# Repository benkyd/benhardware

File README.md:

# BenHardware

A collection of hardware projects, primarily in KiCad

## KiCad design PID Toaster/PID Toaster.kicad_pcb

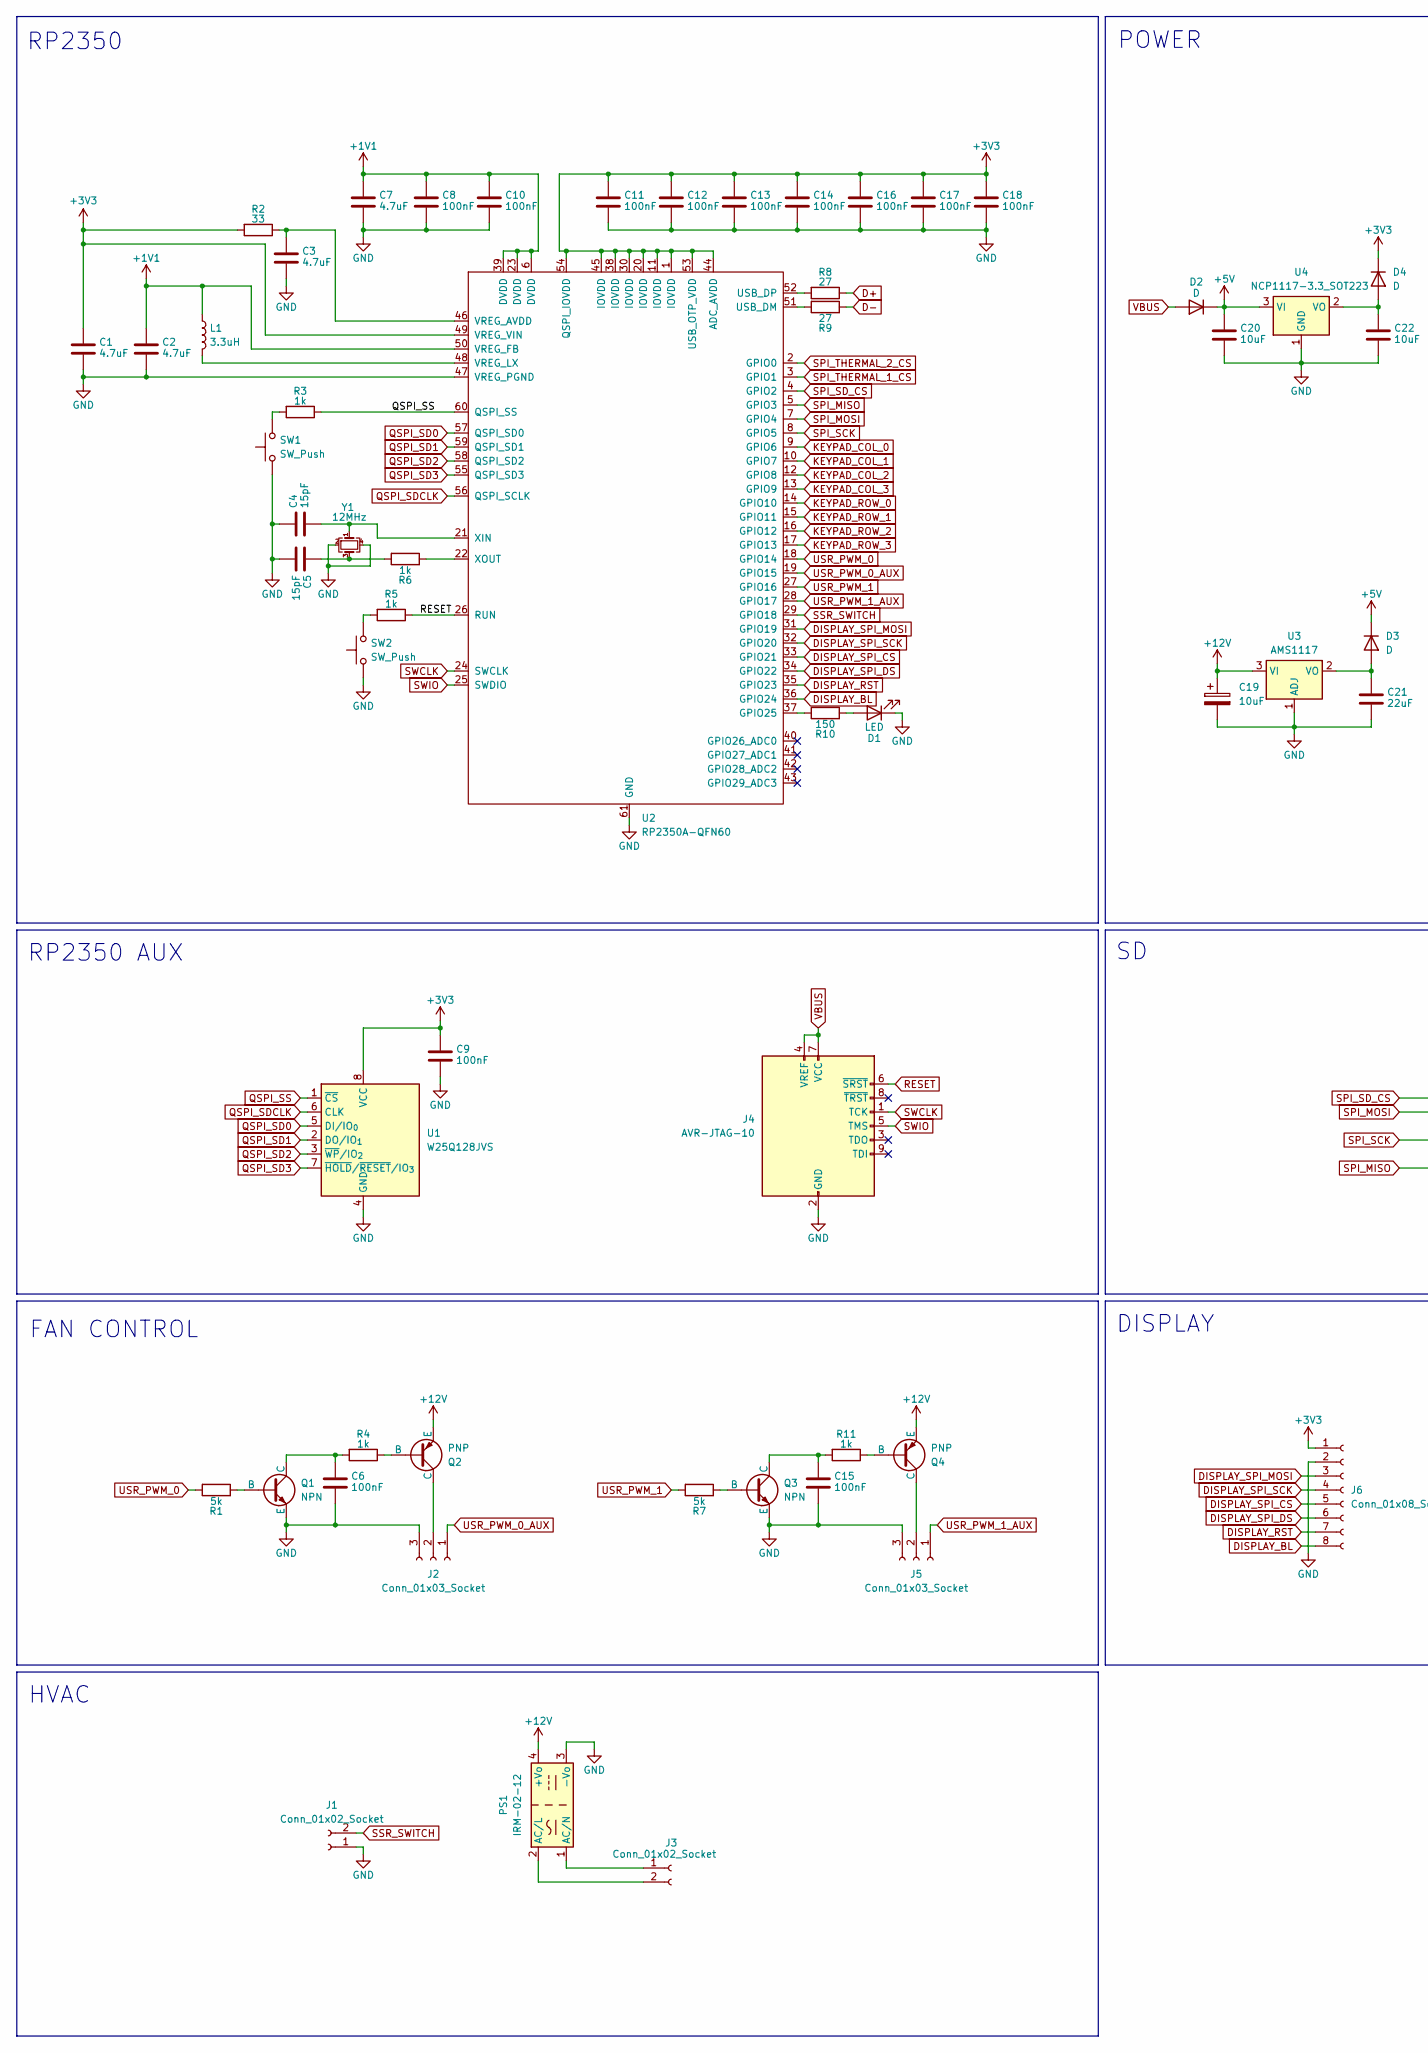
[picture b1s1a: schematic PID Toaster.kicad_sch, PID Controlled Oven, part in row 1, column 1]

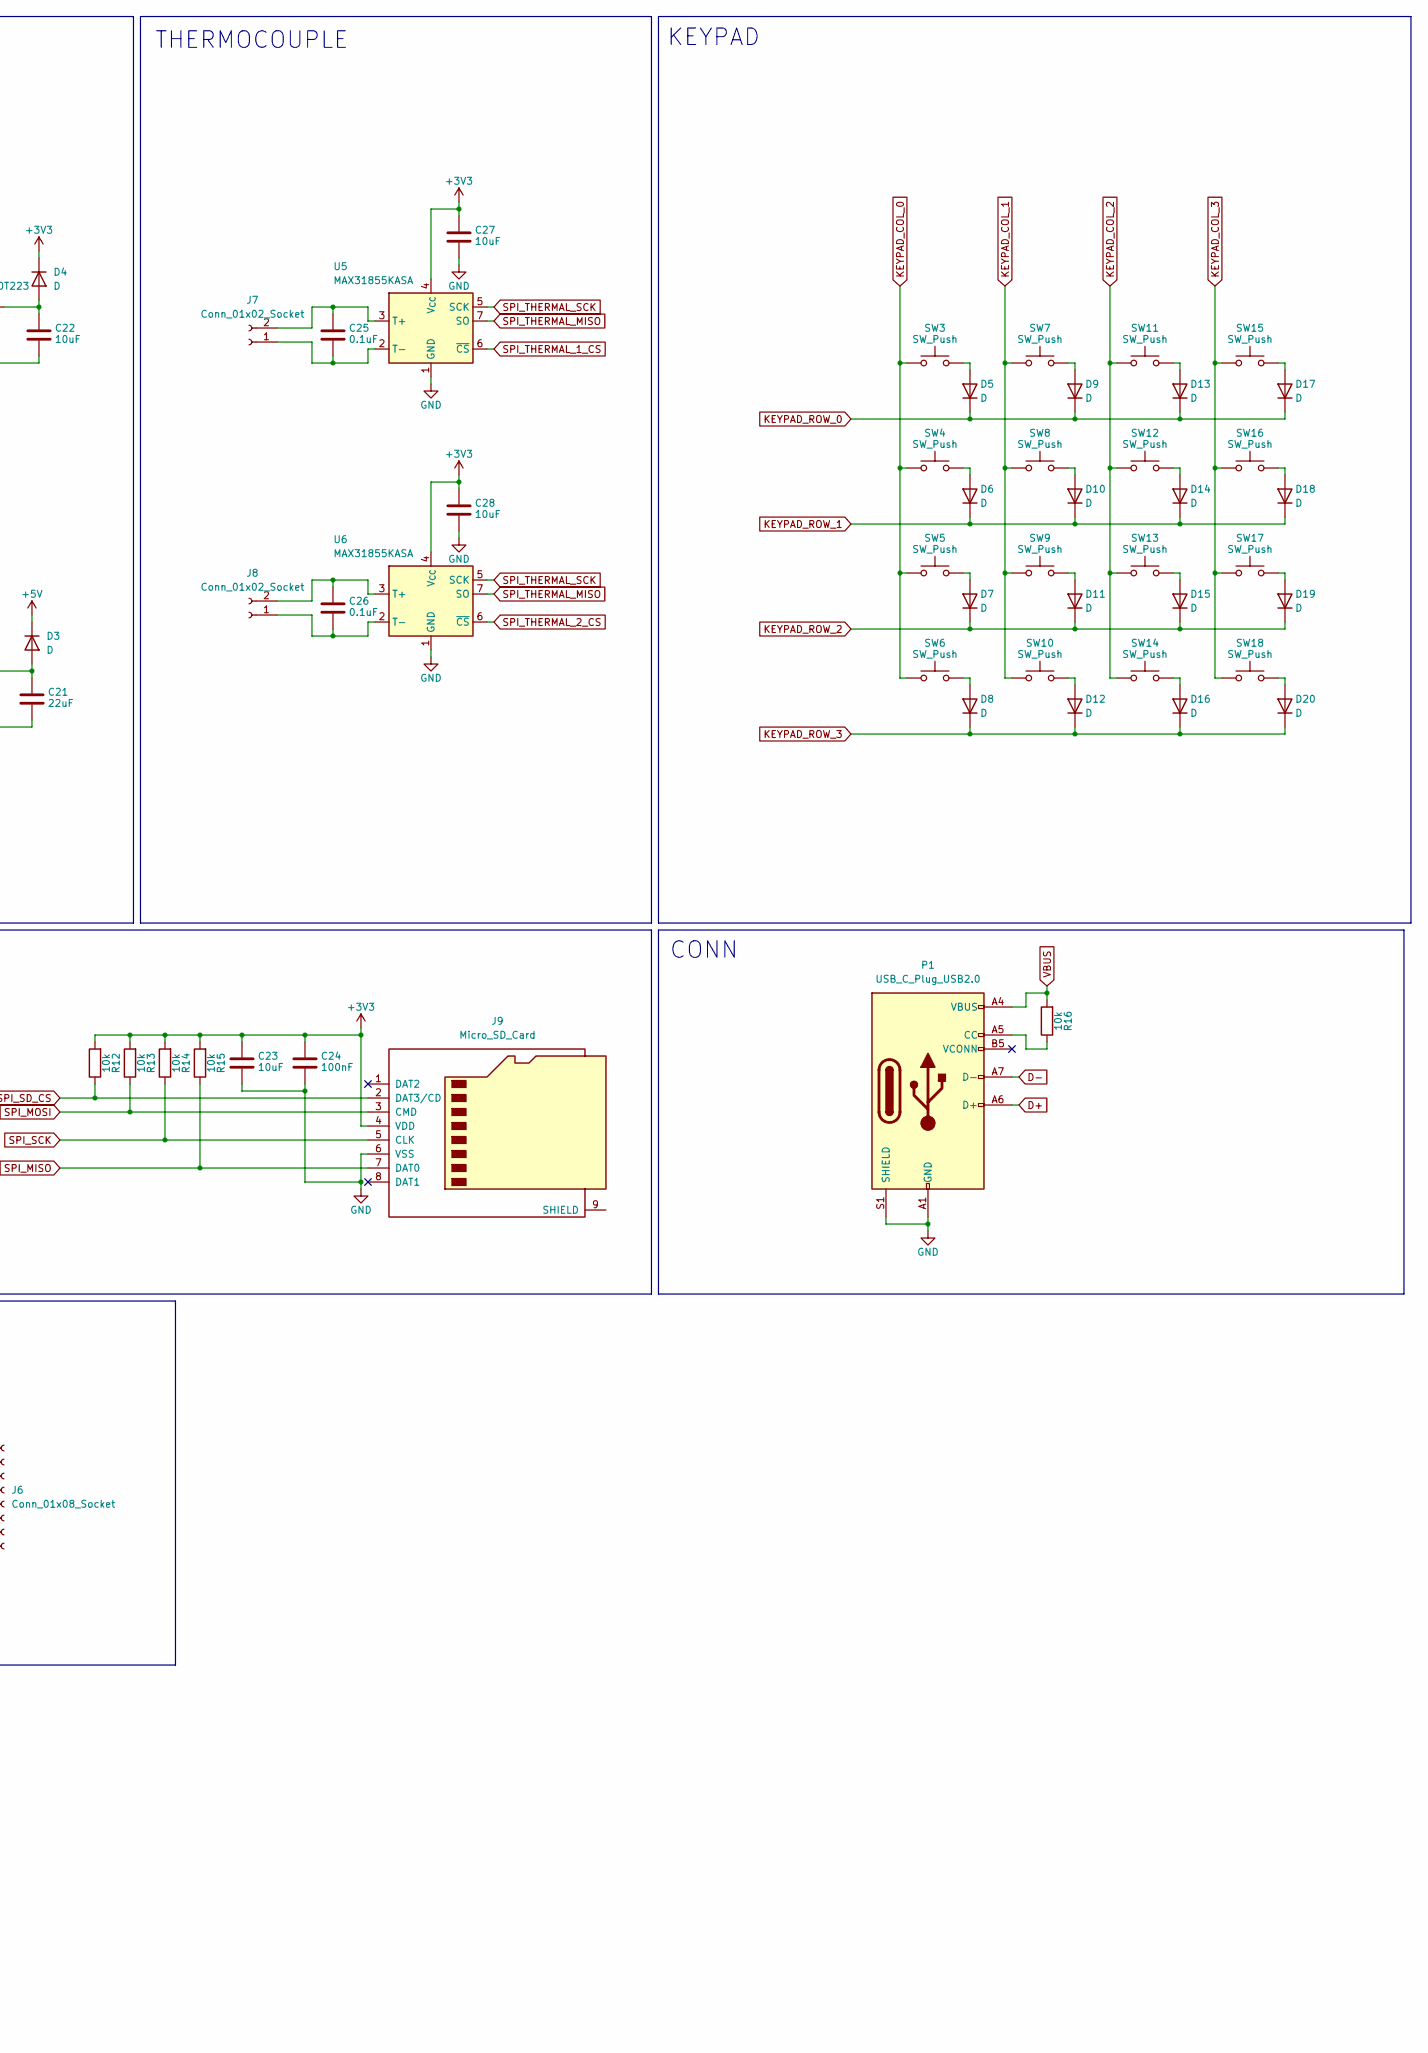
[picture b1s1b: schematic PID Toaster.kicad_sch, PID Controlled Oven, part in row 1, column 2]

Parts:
C1, C2, C3, C7: 4.7uF; C_0805_2012Metric_Pad1.18x1.45mm_HandSolder
C4, C5: 15pF; C_0805_2012Metric_Pad1.18x1.45mm_HandSolder
C6, C8, C9, C10, C11, C12, C13, C14, C15, C16, C17, C18, C24: 100nF; C_0805_2012Metric_Pad1.18x1.45mm_HandSolder
C19: 10uF; CP_Elec_5x4.4
C20, C22, C23, C27, C28: 10uF; C_0805_2012Metric_Pad1.18x1.45mm_HandSolder
C21: 22uF; C_0805_2012Metric_Pad1.18x1.45mm_HandSolder
C25, C26: 0.1uF; C_0805_2012Metric_Pad1.18x1.45mm_HandSolder
D1: LED; LED_0805_2012Metric_Pad1.15x1.40mm_HandSolder
D2, D3, D4: D; D_2010_5025Metric
D5, D6, D7, D8, D9, D10, D11, D12, D13, D14, D15, D16, D17, D18, D19, D20: D; D_0805_2012Metric_Pad1.15x1.40mm_HandSolder
J1, J3, J7, J8: Conn_01x02_Socket; PhoenixContact_MSTBA_2,5_2-G-5,08_1x02_P5.08mm_Horizontal
J2, J5: Conn_01x03_Socket; FanPinHeader_1x03_P2.54mm_Vertical
J4: AVR-JTAG-10; PinHeader_2x05_P1.27mm_Vertical
J6: Conn_01x08_Socket; JST_PH_S8B-PH-K_1x08_P2.00mm_Horizontal
J9: Micro_SD_Card; microSD_HC_Hirose_DM3AT-SF-PEJM5
L1: 3.3uH; L_0603_1608Metric_Pad1.05x0.95mm_HandSolder
P1: USB_C_Plug_USB2.0; USB_C_Receptacle_GCT_USB4105-xx-A_16P_TopMnt_Horizontal
PS1: IRM-02-12; Converter_ACDC_MeanWell_IRM-02-xx_THT
Q1, Q3: NPN; SOT-23
Q2, Q4: PNP; SOT-23
R1, R7: 5k; R_0805_2012Metric_Pad1.20x1.40mm_HandSolder
R2: 33; R_0805_2012Metric_Pad1.20x1.40mm_HandSolder
R3, R4, R5, R6, R11: 1k; R_0805_2012Metric_Pad1.20x1.40mm_HandSolder
R8, R9: 27; R_0805_2012Metric_Pad1.20x1.40mm_HandSolder
R10: 150; R_0805_2012Metric_Pad1.20x1.40mm_HandSolder
R12, R13, R14, R15, R16: 10k; R_0805_2012Metric_Pad1.20x1.40mm_HandSolder
SW1, SW2: SW_Push; SW_Push_1P1T_XKB_TS-1187A
SW3, SW4, SW5, SW6, SW7, SW8, SW9, SW10, SW11, SW12, SW13, SW14, SW15, SW16, SW17, SW18: SW_Push; SW_Cherry_MX_1.00u_PCB
U1: W25Q128JVS; SOIC-8_5.3x5.3mm_P1.27mm
U2: RP2350A-QFN60; RP2350A_QFN-60_EP_7.75x7.75_Pitch0.4mm
U3: AMS1117; SOT-223-3_TabPin2
U4: NCP1117-3.3_SOT223; SOT-223-3_TabPin2; LCSC C26537
U5, U6: MAX31855KASA; SOIC-8_3.9x4.9mm_P1.27mm
Y1: 12MHz; Crystal_SMD_Abracon_ABM8G-4Pin_3.2x2.5mm

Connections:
+1V1: C2.1, C7.1, C8.1, C10.1, L1.1, U2.6 (DVDD), U2.23 (DVDD), U2.39 (DVDD), U2.50 (VREG_FB)
+3V3: C1.1, C9.1, C11.1, C12.1, C13.1, C14.1, C16.1, C17.1, C18.1, C23.1, C24.1, C27.1, C28.1, D4.1 (K), J6.1, J9.4 (VDD), R2.2, R12.2, R13.2, R14.2, R15.2, U1.8 (VCC), U2.1 (IOVDD), U2.11 (IOVDD), U2.20 (IOVDD), U2.30 (IOVDD), U2.38 (IOVDD), U2.44 (ADC_AVDD), U2.45 (IOVDD), U2.49 (VREG_VIN), U2.53 (USB_OTP_VDD), U2.54 (QSPI_IOVDD), U5.4 (V_{CC}), U6.4 (V_{CC})
+5V: C20.1, D2.1 (K), D3.1 (K), U4.3 (VI)
+12V: C19.1, PS1.4 (+Vo), Q2.3 (E), Q4.3 (E), U3.3 (VI)
D+: P1.A6 (D+), R8.1
D-: P1.A7 (D-), R9.2
DISPLAY_BL: J6.8, U2.36 (GPIO24)
DISPLAY_RST: J6.7, U2.35 (GPIO23)
DISPLAY_SPI_CS: J6.5, U2.33 (GPIO21)
DISPLAY_SPI_DS: J6.6, U2.34 (GPIO22)
DISPLAY_SPI_MOSI: J6.3, U2.31 (GPIO19)
DISPLAY_SPI_SCK: J6.4, U2.32 (GPIO20)
GND: C1.2, C2.2, C3.2, C4.1, C5.2, C6.2, C7.2, C8.2, C9.2, C10.2, C11.2, C12.2, C13.2, C14.2, C15.2, C16.2, C17.2, C18.2, C19.2, C20.2, C21.2, C22.2, C23.2, C24.2, C27.2, C28.2, D1.1 (K), J1.1, J2.3, J4.2 (GND), J4.10 (GND), J5.3, J6.2, J9.6 (VSS), P1.A1 (GND), P1.A12 (GND), P1.B1 (GND), P1.B12 (GND), P1.S1 (SHIELD), PS1.3 (-Vo), Q1.3 (E), Q3.3 (E), SW1.1, SW2.1, U1.4 (GND), U2.47 (VREG_PGND), U2.61 (GND), U3.1 (ADJ), U4.1 (GND), U5.1 (GND), U6.1 (GND), Y1.2, Y1.4
KEYPAD_COL_0: SW3.1, SW4.1, SW5.1, SW6.1, U2.9 (GPIO6)
KEYPAD_COL_1: SW7.1, SW8.1, SW9.1, SW10.1, U2.10 (GPIO7)
KEYPAD_COL_2: SW11.1, SW12.1, SW13.1, SW14.1, U2.12 (GPIO8)
KEYPAD_COL_3: SW15.1, SW16.1, SW17.1, SW18.1, U2.13 (GPIO9)
KEYPAD_ROW_0: D5.1 (K), D9.1 (K), D13.1 (K), D17.1 (K), U2.14 (GPIO10)
KEYPAD_ROW_1: D6.1 (K), D10.1 (K), D14.1 (K), D18.1 (K), U2.15 (GPIO11)
KEYPAD_ROW_2: D7.1 (K), D11.1 (K), D15.1 (K), D19.1 (K), U2.16 (GPIO12)
KEYPAD_ROW_3: D8.1 (K), D12.1 (K), D16.1 (K), D20.1 (K), U2.17 (GPIO13)
unnamed: C5.1, R6.1, Y1.3
unnamed: D1.2 (A), R10.2
unnamed: C21.1, D3.2 (A), U3.2 (VO)
unnamed: C22.1, D4.2 (A), U4.2 (VO)
unnamed: D5.2 (A), SW3.2
unnamed: D6.2 (A), SW4.2
unnamed: D7.2 (A), SW5.2
unnamed: D8.2 (A), SW6.2
unnamed: D9.2 (A), SW7.2
unnamed: D10.2 (A), SW8.2
unnamed: D11.2 (A), SW9.2
unnamed: D12.2 (A), SW10.2
unnamed: D13.2 (A), SW11.2
unnamed: D14.2 (A), SW12.2
unnamed: D15.2 (A), SW13.2
unnamed: D16.2 (A), SW14.2
unnamed: D17.2 (A), SW15.2
unnamed: D18.2 (A), SW16.2
unnamed: D19.2 (A), SW17.2
unnamed: D20.2 (A), SW18.2
unnamed: J2.2, Q2.1 (C)
unnamed: J3.1, PS1.1 (AC/N)
unnamed: J3.2, PS1.2 (AC/L)
unnamed: J5.2, Q4.1 (C)
unnamed: C25.2, J7.1, U5.2 (T-)
unnamed: C25.1, J7.2, U5.3 (T+)
unnamed: C26.2, J8.1, U6.2 (T-)
unnamed: C26.1, J8.2, U6.3 (T+)
unnamed: P1.A5 (CC), R16.1
unnamed: Q1.2 (B), R1.2
unnamed: C6.1, Q1.1 (C), R4.2
unnamed: Q2.2 (B), R4.1
unnamed: Q3.2 (B), R7.2
unnamed: C15.1, Q3.1 (C), R11.2
unnamed: Q4.2 (B), R11.1
unnamed: R3.2, SW1.2
unnamed: R5.2, SW2.2
unnamed: R10.1, U2.37 (GPIO25)
unnamed: R9.1, U2.51 (USB_DM)
unnamed: R8.2, U2.52 (USB_DP)
unnamed: C3.1, R2.1, U2.46 (VREG_AVDD)
unnamed: L1.2, U2.48 (VREG_LX)
unnamed: C4.2, U2.21 (XIN), Y1.1
unnamed: R6.2, U2.22 (XOUT)
QSPI_SD0: U1.5 (DI/IO_{0}), U2.57 (QSPI_SD0)
QSPI_SD1: U1.2 (DO/IO_{1}), U2.59 (QSPI_SD1)
QSPI_SD2: U1.3 (~WP/IO_{2}), U2.58 (QSPI_SD2)
QSPI_SD3: U1.7 (~HOLD/~RESET/IO_{3}), U2.55 (QSPI_SD3)
QSPI_SDCLK: U1.6 (CLK), U2.56 (QSPI_SCLK)
QSPI_SS: R3.1, U1.1 (~CS), U2.60 (QSPI_SS)
RESET: J4.6 (~SRST), R5.1, U2.26 (RUN)
SPI_MISO: J9.7 (DAT0), R15.1, U2.5 (GPIO3)
SPI_MOSI: J9.3 (CMD), R13.1, U2.7 (GPIO4)
SPI_SCK: J9.5 (CLK), R14.1, U2.8 (GPIO5)
SPI_SD_CS: J9.2 (DAT3/CD), R12.1, U2.4 (GPIO2)
SPI_THERMAL_1_CS: U2.3 (GPIO1), U5.6 (~CS)
SPI_THERMAL_2_CS: U2.2 (GPIO0), U6.6 (~CS)
SPI_THERMAL_MISO: U5.7 (SO), U6.7 (SO)
SPI_THERMAL_SCK: U5.5 (SCK), U6.5 (SCK)
SSR_SWITCH: J1.2, U2.29 (GPIO18)
SWCLK: J4.1 (TCK), U2.24 (SWCLK)
SWIO: J4.5 (TMS), U2.25 (SWDIO)
USR_PWM_0: R1.1, U2.18 (GPIO14)
USR_PWM_0_AUX: J2.1, U2.19 (GPIO15)
USR_PWM_1: R7.1, U2.27 (GPIO16)
USR_PWM_1_AUX: J5.1, U2.28 (GPIO17)
VBUS: D2.2 (A), J4.4 (VREF), J4.7 (VCC), P1.A4 (VBUS), P1.A9 (VBUS), P1.B4 (VBUS), P1.B9 (VBUS), R16.2

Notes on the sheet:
RP2350
RP2350 AUX
CONN
POWER
DISPLAY
FAN CONTROL
KEYPAD
HVAC
THERMOCOUPLE

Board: 2 copper layers, 105 parts (25 on the bottom side), 88 nets, no tracks yet.

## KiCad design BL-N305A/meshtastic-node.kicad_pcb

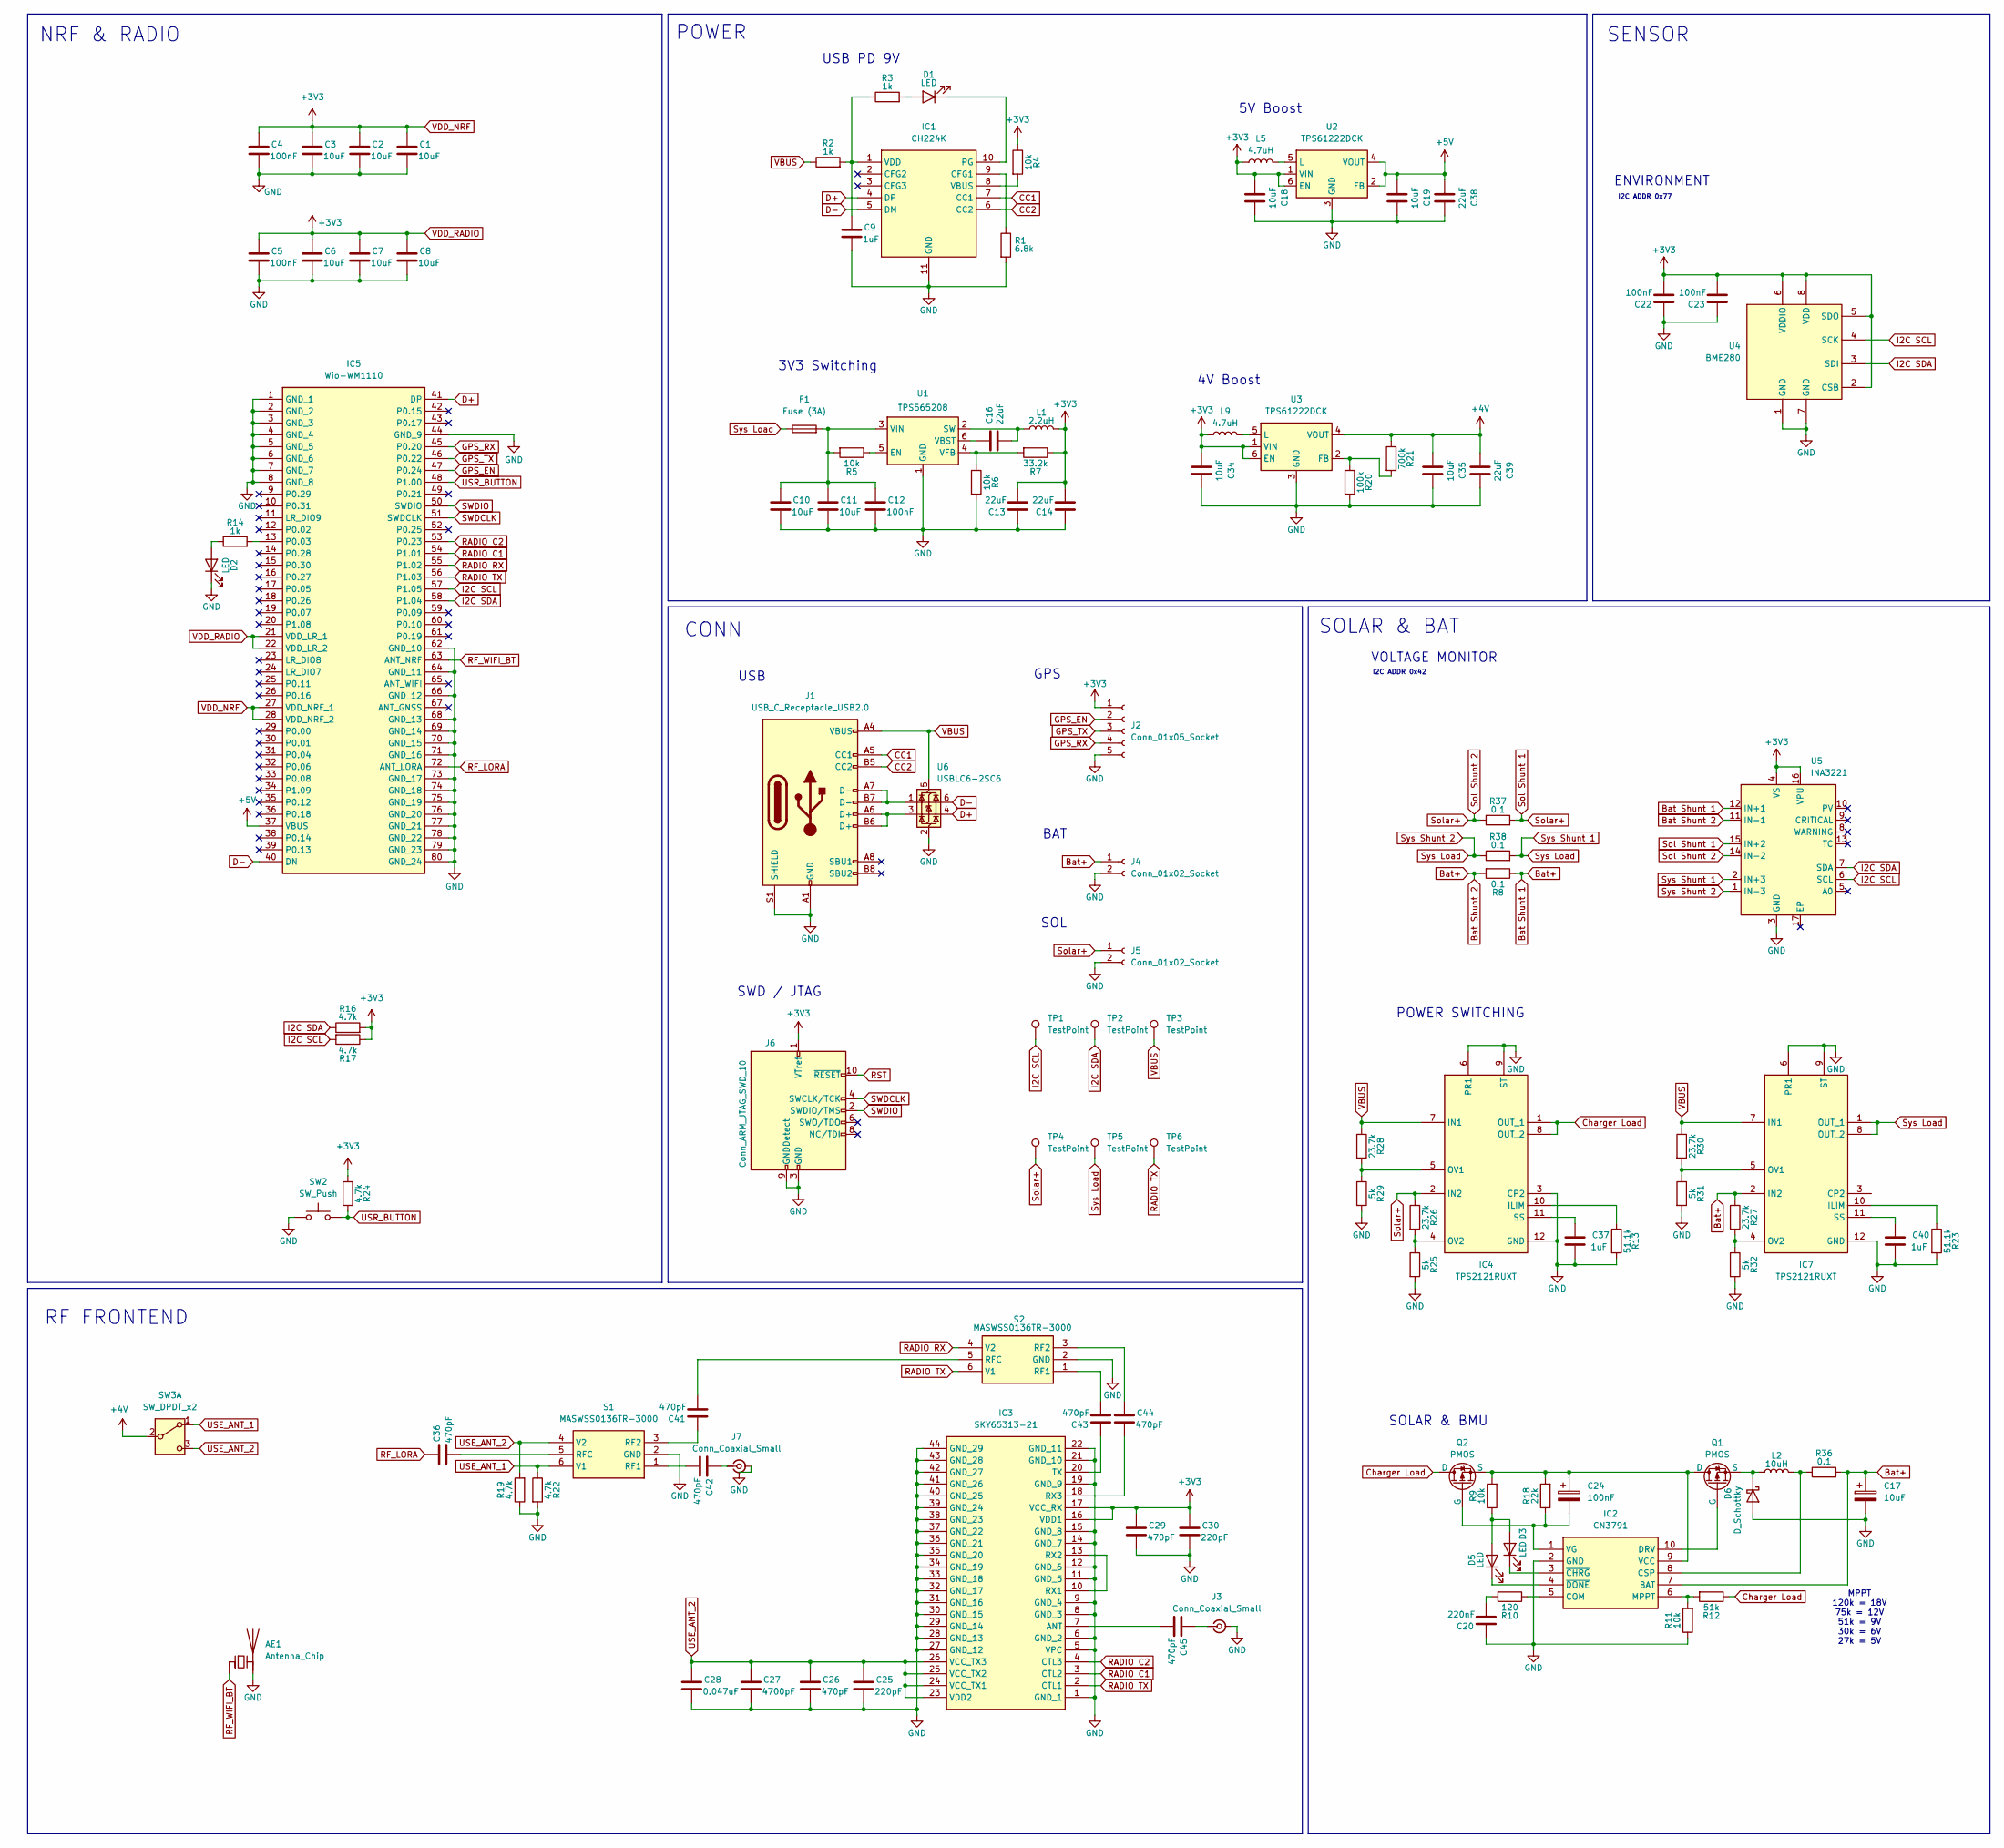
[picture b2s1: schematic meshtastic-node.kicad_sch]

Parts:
AE1: Antenna_Chip; Texas_SWRA117D_2.4GHz_Left
C1, C2, C3, C6, C7, C8, C10, C11, C18, C19, C34, C35: 10uF; C_0805_2012Metric_Pad1.18x1.45mm_HandSolder
C4, C5, C12, C22, C23: 100nF; C_0805_2012Metric_Pad1.18x1.45mm_HandSolder
C9, C37, C40: 1uF; C_0805_2012Metric_Pad1.18x1.45mm_HandSolder
C13, C14, C16, C38, C39: 22uF; C_0805_2012Metric_Pad1.18x1.45mm_HandSolder
C17: 10uF; CP_Elec_4x5.4
C20: 220nF; C_0805_2012Metric_Pad1.18x1.45mm_HandSolder
C24: 100nF; CP_Elec_4x5.4
C25, C30: 220pF; C_0603_1608Metric_Pad1.08x0.95mm_HandSolder
C26, C29, C36, C41, C42, C43, C44, C45: 470pF; C_0603_1608Metric_Pad1.08x0.95mm_HandSolder
C27: 4700pF; C_0603_1608Metric_Pad1.08x0.95mm_HandSolder
C28: 0.047uF; C_0603_1608Metric_Pad1.08x0.95mm_HandSolder
D1, D2, D3, D5: LED; LED_0805_2012Metric_Pad1.15x1.40mm_HandSolder
D6: D_Schottky; D_SOD-123
F1: Fuse (3A); Fuse_0603_1608Metric_Pad1.05x0.95mm_HandSolder
IC1: CH224K; SOP100P600X180-11N; Manufacturer_Part_Number CH224K; LCSC C970725
IC2: CN3791; SOP100P600X175-10N; Manufacturer_Part_Number CN3791; LCSC C154992
IC3: SKY65313-21; SKY6531321; Manufacturer_Part_Number SKY65313-21; Mouser Part Number 873-SKY65313-21
IC4, IC7: TPS2121RUXT; Manufacturer_Part_Number TPS2121RUXT; Mouser Part Number 595-TPS2121RUXT
IC5: Wio-WM1110; WioWM1110; Manufacturer_Part_Number Wio-WM1110
J1: USB_C_Receptacle_USB2.0; USB_C_Receptacle_G-Switch_GT-USB-7010ASV
J2: Conn_01x05_Socket; JST_EH_S5B-EH_1x05_P2.50mm_Horizontal
J3, J7: Conn_Coaxial_Small; SMA_Molex_73251-1153_EdgeMount_Horizontal
J4, J5: Conn_01x02_Socket; JST_EH_S2B-EH_1x02_P2.50mm_Horizontal
J6: Conn_ARM_JTAG_SWD_10; PinHeader_2x05_P1.27mm_Vertical
L1: 2.2uH; L_SXN_SMDRI124; LCSC C2929497
L2: 10uH; L_0805_2012Metric_Pad1.15x1.40mm_HandSolder
L5, L9: 4.7uH; L_0805_2012Metric_Pad1.15x1.40mm_HandSolder
Q1, Q2: PMOS; SOT-23_Handsoldering
R1: 6.8k; R_0805_2012Metric_Pad1.20x1.40mm_HandSolder
R2, R3, R14: 1k; R_0805_2012Metric_Pad1.20x1.40mm_HandSolder
R4, R5, R6, R9, R11: 10k; R_0805_2012Metric_Pad1.20x1.40mm_HandSolder
R7: 33.2k; R_0805_2012Metric_Pad1.20x1.40mm_HandSolder
R8, R36, R37, R38: 0.1; R_2512_6332Metric_Pad1.40x3.35mm_HandSolder
R10: 120; R_0805_2012Metric_Pad1.20x1.40mm_HandSolder
R12: 51k; R_0805_2012Metric_Pad1.20x1.40mm_HandSolder
R13, R23: 51.1k; R_0805_2012Metric_Pad1.20x1.40mm_HandSolder
R16, R17, R19, R22, R24: 4.7k; R_0805_2012Metric_Pad1.20x1.40mm_HandSolder
R18: 22k; R_0805_2012Metric_Pad1.20x1.40mm_HandSolder
R20: 100k; R_0805_2012Metric_Pad1.20x1.40mm_HandSolder
R21: 700k; R_0805_2012Metric_Pad1.20x1.40mm_HandSolder
R25, R29, R31, R32: 5k; R_0805_2012Metric_Pad1.20x1.40mm_HandSolder
R26, R27, R28, R30: 23.7k; R_0805_2012Metric_Pad1.20x1.40mm_HandSolder
S1, S2: MASWSS0136TR-3000; SOT65P210X110-6N; Manufacturer_Part_Number MASWSS0136TR-3000; Mouser Part Number 937-MASWSS0136-T
SW2: SW_Push; SW_Push_1P1T_XKB_TS-1187A; LCSC C42420254
SW3: SW_DPDT_x2; SS3235SL3; LCSC C381098
TP1, TP2, TP3, TP4, TP5, TP6: TestPoint; TestPoint_Pad_D2.0mm
U1: TPS565208; SOT-23-6; LCSC C2650336
U2, U3: TPS61222DCK; Texas_R-PDSO-G6; LCSC C116461
U4: BME280; Bosch_LGA-8_2.5x2.5mm_P0.65mm_ClockwisePinNumbering; LCSC C92489
U5: INA3221; Texas_RGV0016A_VQFN-16-1EP_4x4mm_P0.65mm_EP2.1x2.1mm; LCSC C181255
U6: USBLC6-2SC6; SOT-23-6

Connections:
+4V: C35.1, C39.1, R21.1, SW3.2 (B), U3.4 (VOUT)
+5V: C19.1, C38.1, IC5.37 (VBUS), U2.2 (FB), U2.4 (VOUT)
Bat Shunt 1: C17.1, IC2.7 (BAT), IC7.2 (IN2), J4.1, R8.1, R8.2, R27.1, R36.2, U5.11 (IN-1), U5.12 (IN+1)
CC1: IC1.7 (CC1), J1.A5 (CC1)
CC2: IC1.6 (CC2), J1.B5 (CC2)
Charger Load: IC4.1 (OUT_1), IC4.8 (OUT_2), Q2.1 (D), R12.1
D+: IC1.4 (DP), IC5.41 (DP), U6.4 (I/O2)
D-: IC1.5 (DM), IC5.40 (DN), U6.6 (I/O1)
GND: AE1.2 (PCB_Trace), C1.2, C2.2, C3.2, C4.2, C5.2, C6.2, C7.2, C8.2, C9.2, C10.2, C11.2, C12.2, C13.1, C14.1, C17.2, C18.2, C19.2, C20.1, C22.1, C23.1, C25.2, C26.2, C27.2, C28.2, C29.2, C30.2, C34.2, C35.2, C37.2, C38.2, C39.2, C40.2, D2.1 (K), D6.2 (A), IC1.11 (GND), IC2.2 (GND), IC3.1 (GND_1), IC3.5 (VPC), IC3.6 (GND_2), IC3.8 (GND_3), IC3.9 (GND_4), IC3.11 (GND_5), IC3.12 (GND_6), IC3.14 (GND_7), IC3.15 (GND_8), IC3.19 (GND_9), IC3.21 (GND_10), IC3.22 (GND_11), IC3.27 (GND_12), IC3.28 (GND_13), IC3.29 (GND_14), IC3.30 (GND_15), IC3.31 (GND_16), IC3.32 (GND_17), IC3.33 (GND_18), IC3.34 (GND_19), IC3.35 (GND_20), IC3.36 (GND_21), IC3.37 (GND_22), IC3.38 (GND_23), IC3.39 (GND_24), IC3.40 (GND_25), IC3.41 (GND_26), IC3.42 (GND_27), IC3.43 (GND_28), IC3.44 (GND_29), IC4.3 (CP2), IC4.6 (PR1), IC4.9 (ST), IC4.12 (GND), IC5.1 (GND_1), IC5.2 (GND_2), IC5.3 (GND_3), IC5.4 (GND_4), IC5.5 (GND_5), IC5.6 (GND_6), IC5.7 (GND_7), IC5.8 (GND_8), IC5.44 (GND_9), IC5.62 (GND_10), IC5.64 (GND_11), IC5.66 (GND_12), IC5.68 (GND_13), IC5.69 (GND_14), IC5.70 (GND_15), IC5.71 (GND_16), IC5.73 (GND_17), IC5.74 (GND_18), IC5.75 (GND_19), IC5.76 (GND_20), IC5.77 (GND_21), IC5.78 (GND_22), IC5.79 (GND_23), IC5.80 (GND_24), IC7.6 (PR1), IC7.9 (ST), IC7.12 (GND), J1.A1 (GND), J1.A12 (GND), J1.B1 (GND), J1.B12 (GND), J1.S1 (SHIELD), J2.5, J3.2 (Ext), J4.2, J5.2, J6.3 (GND), J6.5 (GND), J6.9 (GNDDetect), J7.2 (Ext), R1.2, R6.2, R11.1, R13.2, R19.1, R20.2, R22.2, R23.2, R25.2, R29.2, R31.2, R32.2, S1.2 (GND), S2.2 (GND), SW2.1, U1.1 (GND), U2.3 (GND), U3.3 (GND), U4.1 (GND), U4.7 (GND), U5.3 (GND), U6.2 (GND)
GPS_EN: IC5.47 (P0.24), J2.2
GPS_RX: IC5.45 (P0.20), J2.4
GPS_TX: IC5.46 (P0.22), J2.3
I2C SCL: IC5.57 (P1.05), R17.2, TP1.1, U4.4 (SCK), U5.6 (SCL)
I2C SDA: IC5.58 (P1.04), R16.1, TP2.1, U4.3 (SDI), U5.7 (SDA)
unnamed: C20.2, R10.2
unnamed: D1.2 (A), R3.2
unnamed: D1.1 (K), IC1.10 (PG)
unnamed: D2.2 (A), R14.1
unnamed: D3.2 (A), D5.2 (A), R9.1
unnamed: D3.1 (K), IC2.3 (~CHRG)
unnamed: D5.1 (K), IC2.4 (~DONE)
unnamed: D6.1 (K), L2.1, Q1.3 (S)
unnamed: IC1.9 (CFG1), R1.1
unnamed: IC1.8 (VBUS), R4.2
unnamed: C9.1, IC1.1 (VDD), R2.2, R3.1
unnamed: IC2.5 (COM), R10.1
unnamed: IC2.8 (CSP), L2.2, R36.1
unnamed: IC2.10 (DRV), Q1.2 (G)
unnamed: IC2.6 (MPPT), R11.2, R12.2
unnamed: C24.1, IC2.9 (VCC), Q1.1 (D), Q2.3 (S), R9.2, R18.2
unnamed: C24.2, IC2.1 (VG), Q2.2 (G), R18.1
unnamed: C45.2, IC3.7 (ANT)
unnamed: IC3.10 (RX1), IC3.13 (RX2)
unnamed: C44.2, IC3.18 (RX3)
unnamed: C43.1, IC3.20 (TX)
unnamed: IC4.10 (ILIM), R13.1
unnamed: IC4.5 (OV1), R28.2, R29.1
unnamed: IC4.4 (OV2), R25.1, R26.2
unnamed: C37.1, IC4.11 (SS)
unnamed: IC5.13 (P0.03), R14.2
unnamed: IC7.10 (ILIM), R23.1
unnamed: IC7.5 (OV1), R30.2, R31.1
unnamed: IC7.4 (OV2), R27.2, R32.1
unnamed: C40.1, IC7.11 (SS)
unnamed: J1.A6 (D+), J1.B6 (D+), U6.3 (I/O2)
unnamed: J1.A7 (D-), J1.B7 (D-), U6.1 (I/O1)
unnamed: C45.1, J3.1 (In)
unnamed: C42.1, J7.1 (In)
unnamed: C42.2, S1.1 (RF1)
unnamed: C41.1, S1.3 (RF2)
unnamed: C36.2, S1.5 (RFC)
unnamed: C43.2, S2.1 (RF1)
unnamed: C44.1, S2.3 (RF2)
unnamed: C41.2, S2.5 (RFC)
unnamed: R5.1, U1.5 (EN)
unnamed: C16.2, L1.1, U1.2 (SW)
unnamed: C16.1, U1.6 (VBST)
unnamed: R6.1, R7.2, U1.4 (VFB)
unnamed: C10.1, C11.1, C12.1, F1.2, R5.2, U1.3 (VIN)
unnamed: L5.2, U2.5 (L)
unnamed: R20.1, R21.2, U3.2 (FB)
unnamed: L9.2, U3.5 (L)
RADIO C1: IC3.3 (CTL2), IC5.54 (P1.01)
RADIO C2: IC3.4 (CTL3), IC5.53 (P0.23)
RADIO RX: IC5.55 (P1.02), S2.4 (V2)
RADIO TX: IC3.2 (CTL1), IC5.56 (P1.03), S2.6 (V1), TP6.1
RF_LORA: C36.1, IC5.72 (ANT_LORA)
RF_WIFI_BT: AE1.1 (FEED), IC5.63 (ANT_NRF)
RST: J6.10 (~RESET)
SWDCLK: IC5.51 (SWDCLK), J6.4 (SWCLK/TCK)
SWDIO: IC5.50 (SWDIO), J6.2 (SWDIO/TMS)
Sol Shunt 1: IC4.2 (IN2), J5.1, R26.1, R37.1, R37.2, TP4.1, U5.14 (IN-2), U5.15 (IN+2)
Sys Load: F1.1, IC7.1 (OUT_1), IC7.8 (OUT_2), R38.1, R38.2, TP5.1, U5.1 (IN-3), U5.2 (IN+3)
USE_ANT_1: R22.1, S1.6 (V1), SW3.1 (A)
USE_ANT_2: C25.1, C26.1, C27.1, C28.1, IC3.23 (VDD2), IC3.24 (VCC_TX1), IC3.25 (VCC_TX2), IC3.26 (VCC_TX3), R19.2, S1.4 (V2), SW3.3 (C)
USR_BUTTON: IC5.48 (P1.00), R24.2, SW2.2
VBUS: IC4.7 (IN1), IC7.7 (IN1), J1.A4 (VBUS), J1.A9 (VBUS), J1.B4 (VBUS), J1.B9 (VBUS), R2.1, R28.1, R30.1, TP3.1, U6.5 (VBUS)
VDD_NRF: C1.1, C2.1, C3.1, C4.1, C5.1, C6.1, C7.1, C8.1, C13.2, C14.2, C18.1, C22.2, C23.2, C29.1, C30.1, C34.1, IC3.16 (VDD1), IC3.17 (VCC_RX), IC5.21 (VDD_LR_1), IC5.22 (VDD_LR_2), IC5.27 (VDD_NRF_1), IC5.28 (VDD_NRF_2), J2.1, J6.1 (VTref), L1.2, L5.1, L9.1, R4.1, R7.1, R16.2, R17.1, R24.1, U2.1 (VIN), U2.6 (EN), U3.1 (VIN), U3.6 (EN), U4.2 (CSB), U4.5 (SDO), U4.6 (VDDIO), U4.8 (VDD), U5.4 (VS), U5.16 (VPU)

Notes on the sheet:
I2C ADDR 0x77
3V3 Switching
GPS
MPPT 120k = 18V 75k = 12V 51k = 9V 30k = 6V 27k = 5V
ENVIRONMENT
BAT
SENSOR
VOLTAGE MONITOR
5V Boost
CONN
SOL
4V Boost
SOLAR & BAT
SWD / JTAG
I2C ADDR 0x42
NRF & RADIO
USB PD 9V
SOLAR & BMU
POWER
USB
RF FRONTEND
POWER SWITCHING

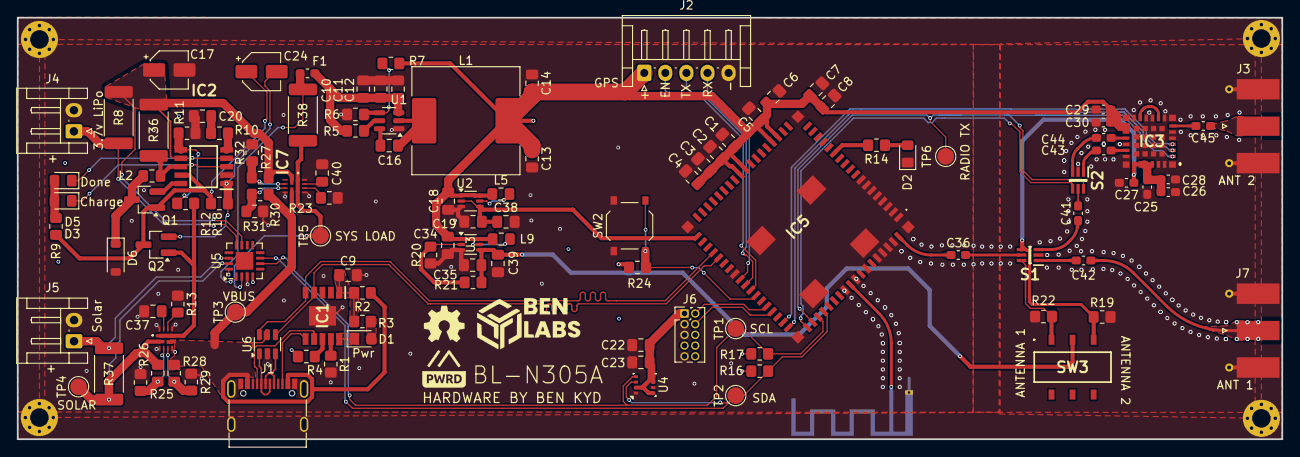
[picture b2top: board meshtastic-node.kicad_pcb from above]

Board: 4 copper layers, 150.0 x 50.0 mm, 116 parts (1 on the bottom side), 77 nets.

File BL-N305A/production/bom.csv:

Designator,Footprint,Quantity,Value,LCSC Part #
AE1,Texas_SWRA117D_2.4GHz_Left,1,Antenna_Chip,
"C1, C10, C11, C18, C19, C2, C3, C34, C35, C6, C7, C8",0805,12,10uF,
"C12, C22, C23, C4, C5",0805,5,100nF,
"C13, C14, C16, C38, C39",0805,5,22uF,
C17,CP_Elec_4x5.4,1,10uF,
C20,0805,1,220nF,
C24,CP_Elec_4x5.4,1,100nF,
"C25, C30",0603,2,220pF,
"C26, C29, C36, C41, C42, C43, C44, C45",0603,8,470pF,
C27,0603,1,4700pF,
C28,0603,1,0.047uF,
"C37, C40, C9",0805,3,1uF,
"D1, D2, D3, D5",0805,4,LED,
D6,D_SOD-123,1,D_Schottky,
F1,0603,1,Fuse (3A),
IC1,SOP100P600X180-11N,1,CH224K,C970725
IC2,SOP100P600X175-10N,1,CN3791,C154992
IC3,SKY6531321,1,SKY65313-21,C5144140
"IC4, IC7",TPS2121RUXT,2,TPS2121RUXT,C2156025
IC5,WioWM1110,1,Wio-WM1110,
J1,USB_C_Receptacle_G-Switch_GT-USB-7010ASV,1,USB_C_Receptacle_USB2.0,
J2,JST_EH_S5B-EH_1x05_P2.50mm_Horizontal,1,Conn_01x05_Socket,
"J3, J7",SMA_Molex_73251-1153_EdgeMount_Horizontal,2,Conn_Coaxial_Small,
"J4, J5",JST_EH_S2B-EH_1x02_P2.50mm_Horizontal,2,Conn_01x02_Socket,
J6,PinHeader_2x05_P1.27mm_Vertical,1,Conn_ARM_JTAG_SWD_10,
L1,L_SXN_SMDRI124,1,2.2uH,C2929497
L2,0805,1,10uH,
"L5, L9",0805,2,4.7uH,
"Q1, Q2",SOT-23_Handsoldering,2,PMOS,
R1,0805,1,6.8k,
R10,0805,1,120,
"R11, R4, R5, R6, R9",0805,5,10k,
R12,0805,1,51k,
"R13, R23",0805,2,51.1k,
"R14, R2, R3",0805,3,1k,
"R16, R17, R19, R22, R24",0805,5,4.7k,
R18,0805,1,22k,
R20,0805,1,100k,
R21,0805,1,700k,
"R25, R29, R31, R32",0805,4,5k,
"R26, R27, R28, R30",0805,4,23.7k,
"R36, R37, R38, R8",2512,4,0.1,
R7,0805,1,33.2k,
"S1, S2",SOT65P210X110-6N,2,MASWSS0136TR-3000,
SW2,SW_Push_1P1T_XKB_TS-1187A,1,SW_Push,C42420254
SW3,SS3235SL3,1,SW_DPDT_x2,C381098
"TP1, TP2, TP3, TP4, TP5, TP6",TestPoint_Pad_D2.0mm,6,TestPoint,
U1,SOT-23-6,1,TPS565208,C2650336
U2,Texas_R-PDSO-G6,1,TPS61222DCK,C116461
U3,Texas_R-PDSO-G6,1,TPS61222DCK,C116461 
U4,Bosch_LGA-8_2.5x2.5mm_P0.65mm_ClockwisePinNumbering,1,BME280,C92489
U5,Texas_RGV0016A_VQFN-16-1EP_4x4mm_P0.65mm_EP2.1x2.1mm,1,INA3221,C181255
U6,SOT-23-6,1,USBLC6-2SC6,
